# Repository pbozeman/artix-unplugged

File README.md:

# Artix Unplugged

Bare Artix-7 with all the IO pins exposed.

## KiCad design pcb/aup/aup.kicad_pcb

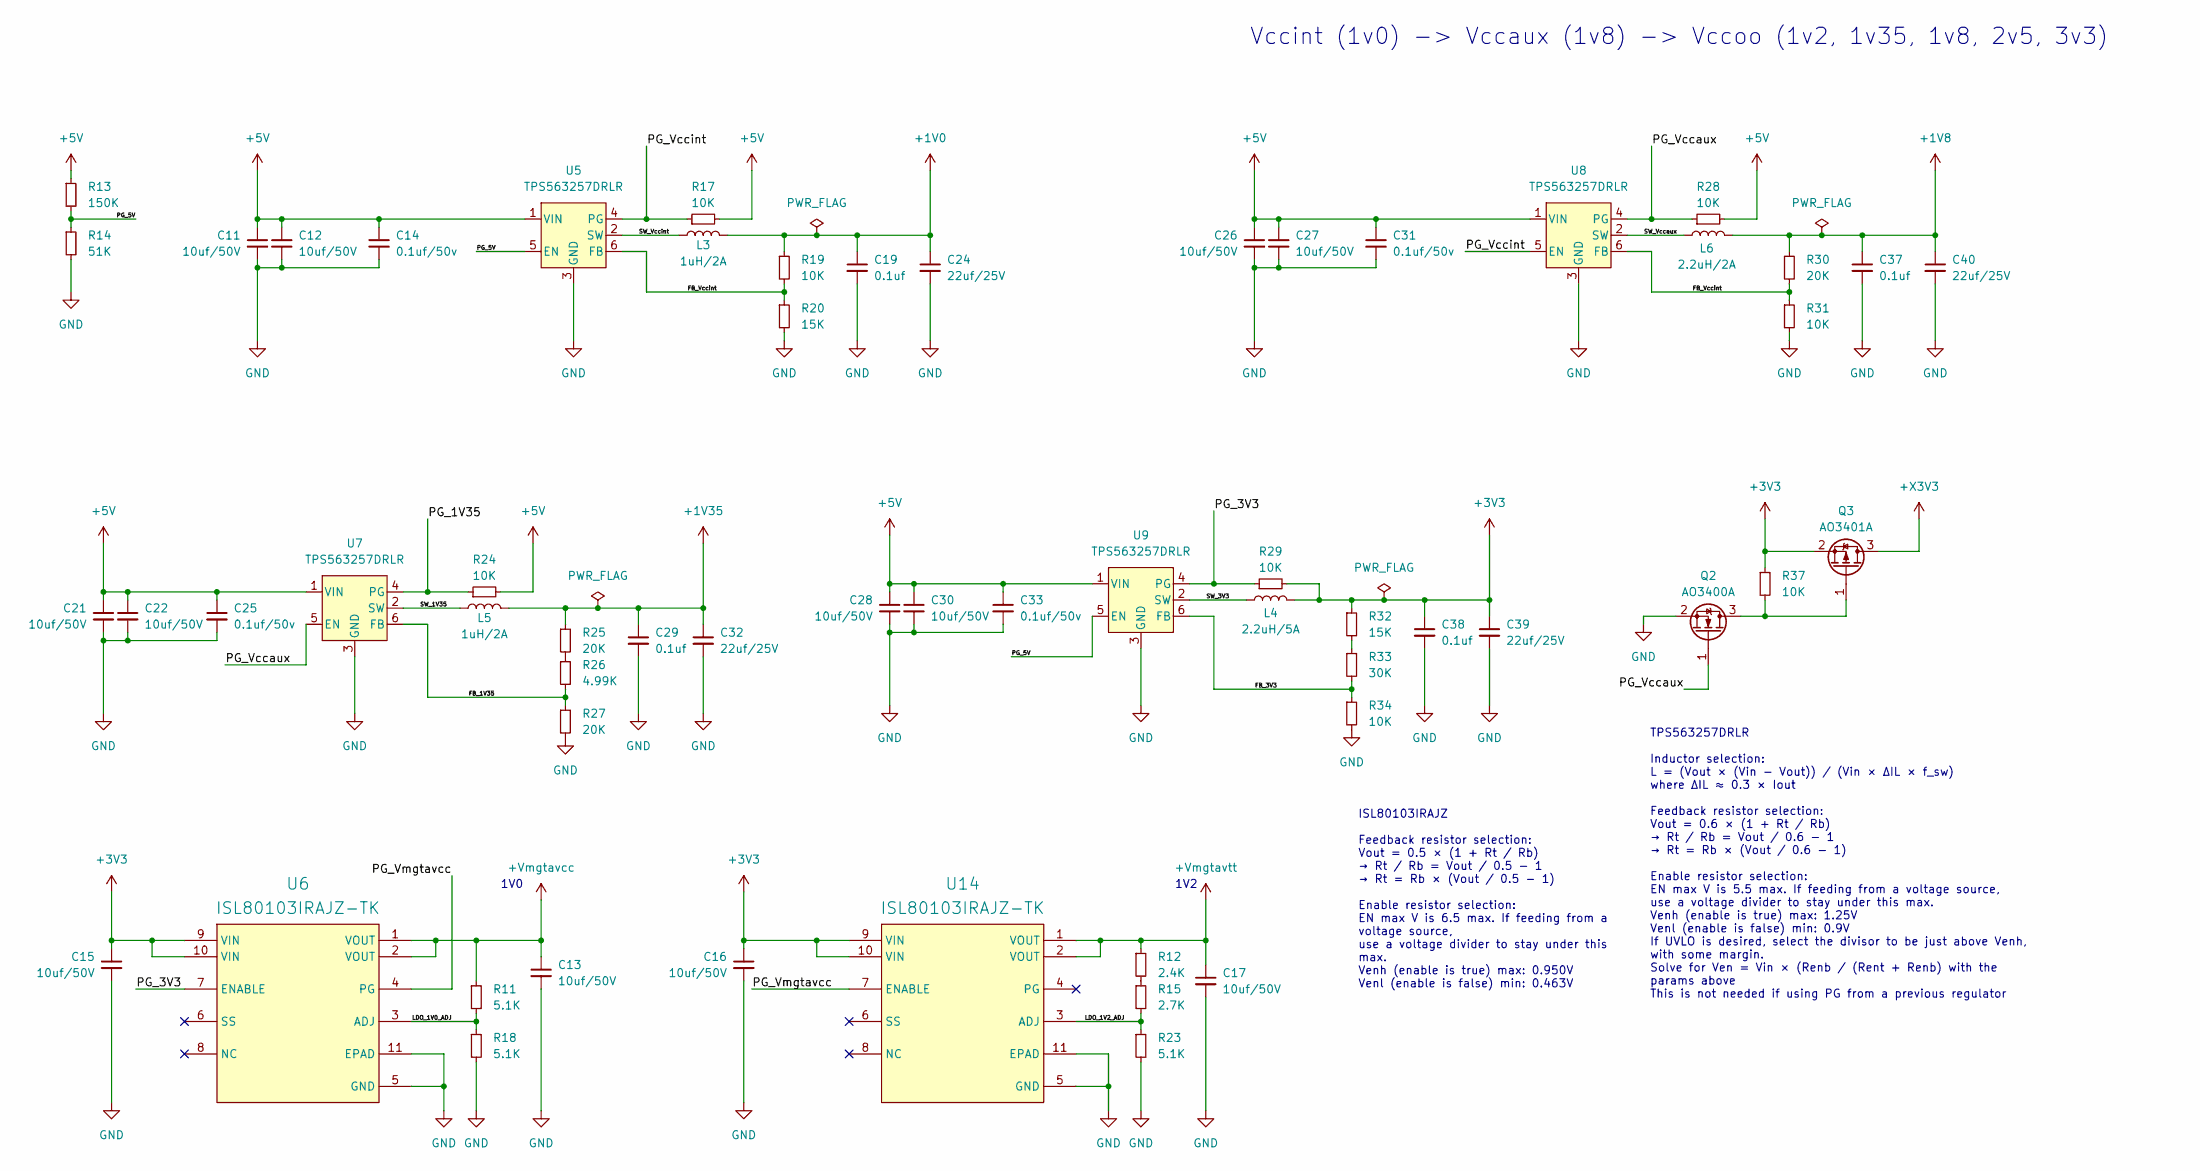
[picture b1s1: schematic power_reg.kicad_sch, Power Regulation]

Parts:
C11, C12, C13, C15, C16, C17, C21, C22, C26, C27, C28, C30: 10uf/50V; C_0805_2012Metric; LCSC Part # C440198
C14, C25, C31, C33: 0.1uf/50v; C_0603_1608Metric; LCSC Part # C14663
C19, C29, C37, C38: 0.1uf; C_0402_1005Metric; LCSC Part # C1525
C24, C32, C39, C40: 22uf/25V; C_0805_2012Metric; LCSC Part # C45783
L3, L5: 1uH/2A; L_1008_2520Metric; LCSC Part # C435392
L4: 2.2uH/5A; L_Sunlord_MWSA0518S; LCSC Part # C408345
L6: 2.2uH/2A; L_1008_2520Metric; LCSC Part # C576403
Q2: AO3400A; SOT-23; LCSC Part # C20917
Q3: AO3401A; SOT-23; LCSC Part # C15127
R11, R18, R23: 5.1K; R_0603_1608Metric; LCSC Part # C23186
R12: 2.4K; R_0603_1608Metric; LCSC Part # C22940
R13: 150K; R_0603_1608Metric; LCSC Part # C22808
R14: 51K; R_0603_1608Metric; LCSC Part # C23196
R15: 2.7K; R_0603_1608Metric; LCSC Part # C25879
R17, R19, R24, R28, R29, R31, R34, R37: 10K; R_0603_1608Metric; LCSC Part # C25804
R20, R32: 15K; R_0603_1608Metric; LCSC Part # C22809
R25, R27, R30: 20K; R_0603_1608Metric; LCSC Part # C4184
R26: 4.99K; R_0603_1608Metric; LCSC Part # C23046
R33: 30K; R_0603_1608Metric; LCSC Part # C22984
U5, U7, U8, U9: TPS563257DRLR; SOT6_DRL_TEX; LCSC Part # C20539656
U6, U14: ISL80103IRAJZ-TK; DFN10_3X3_INR; LCSC Part # C382020

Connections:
+1V0: C19.1, C24.1, L3.2, R19.1; also elsewhere on the board
+1V8: C37.1, C40.1, L6.2, R30.1; also elsewhere on the board
+1V35: C29.1, C32.1, L5.2, R25.1; also elsewhere on the board
+3V3: C15.1, C16.1, C38.1, C39.1, L4.2, Q3.2 (S), R29.2, R32.1, R37.1, U6.9 (VIN), U6.10 (VIN), U14.9 (VIN), U14.10 (VIN); also elsewhere on the board
+5V: C11.1, C12.1, C14.1, C21.1, C22.1, C25.1, C26.1, C27.1, C28.1, C30.1, C31.1, C33.1, R13.1, R17.2, R24.2, R28.2, U5.1 (VIN), U7.1 (VIN), U8.1 (VIN), U9.1 (VIN); also elsewhere on the board
+Vmgtavcc: C13.1, R11.1, U6.1 (VOUT), U6.2 (VOUT); also elsewhere on the board
+Vmgtavtt: C17.1, R12.1, U14.1 (VOUT), U14.2 (VOUT); also elsewhere on the board
+X3V3: Q3.3 (D)
/power_reg/FB_1V35: R26.2, R27.1, U7.6 (FB)
/power_reg/FB_3V3: R33.2, R34.1, U9.6 (FB)
/power_reg/FB_Vccint: R19.2, R20.1, R30.2, R31.1, U5.6 (FB), U8.6 (FB)
/power_reg/LDO_1V0_ADJ: R11.2, R18.1, U6.3 (ADJ)
/power_reg/LDO_1V2_ADJ: R15.2, R23.1, U14.3 (ADJ)
/power_reg/PG_1V35: R24.1, U7.4 (PG)
/power_reg/PG_3V3: R29.1, U6.7 (ENABLE), U9.4 (PG)
/power_reg/PG_5V: R13.2, R14.1, U5.5 (EN), U9.5 (EN)
/power_reg/PG_Vccaux: Q2.1 (G), R28.1, U7.5 (EN), U8.4 (PG)
/power_reg/PG_Vccint: R17.1, U5.4 (PG), U8.5 (EN)
/power_reg/PG_Vmgtavcc: U6.4 (PG), U14.7 (ENABLE)
/power_reg/SW_1V35: L5.1, U7.2 (SW)
/power_reg/SW_3V3: L4.1, U9.2 (SW)
/power_reg/SW_Vccaux: L6.1, U8.2 (SW)
/power_reg/SW_Vccint: L3.1, U5.2 (SW)
GND: C11.2, C12.2, C13.2, C14.2, C15.2, C16.2, C17.2, C19.2, C21.2, C22.2, C24.2, C25.2, C26.2, C27.2, C28.2, C29.2, C30.2, C31.2, C32.2, C33.2, C37.2, C38.2, C39.2, C40.2, Q2.2 (S), R14.2, R18.2, R20.2, R23.2, R27.2, R31.2, R34.2, U5.3 (GND), U6.5 (GND), U6.11 (EPAD), U7.3 (GND), U8.3 (GND), U9.3 (GND), U14.5 (GND), U14.11 (EPAD); also elsewhere on the board
unnamed: Q2.3 (D), Q3.1 (G), R37.2
unnamed: R12.2, R15.1
unnamed: R25.2, R26.1
unnamed: R32.2, R33.1

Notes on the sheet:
Vccint (1v0) -> Vccaux (1v8) -> Vccoo (1v2, 1v35, 1v8, 2v5, 3v3)
1V2
1V0
TPS563257DRLR Inductor selection: L = (Vout × (Vin - Vout)) / (Vin × ΔIL × f_sw) where ΔIL ≈ 0.3 × Iout Feedback resistor selection: Vout = 0.6 × (1 + Rt / Rb) → Rt / Rb = Vout / 0.6 - 1 → Rt = Rb × (Vout / 0.6 - 1) Enable resistor selection: EN max V is 5.5 max. If feeding from a voltage source, u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
ISL80103IRAJZ Feedback resistor selection: Vout = 0.5 × (1 + Rt / Rb) → Rt / Rb = Vout / 0.5 - 1 → Rt = Rb × (Vout / 0.5 - 1) Enable resistor selection: EN max V is 6.5 max. If feeding from a voltage source, use a voltage divider to stay under this max. Venh (enable is true) max: 0.950V Venl (enabl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

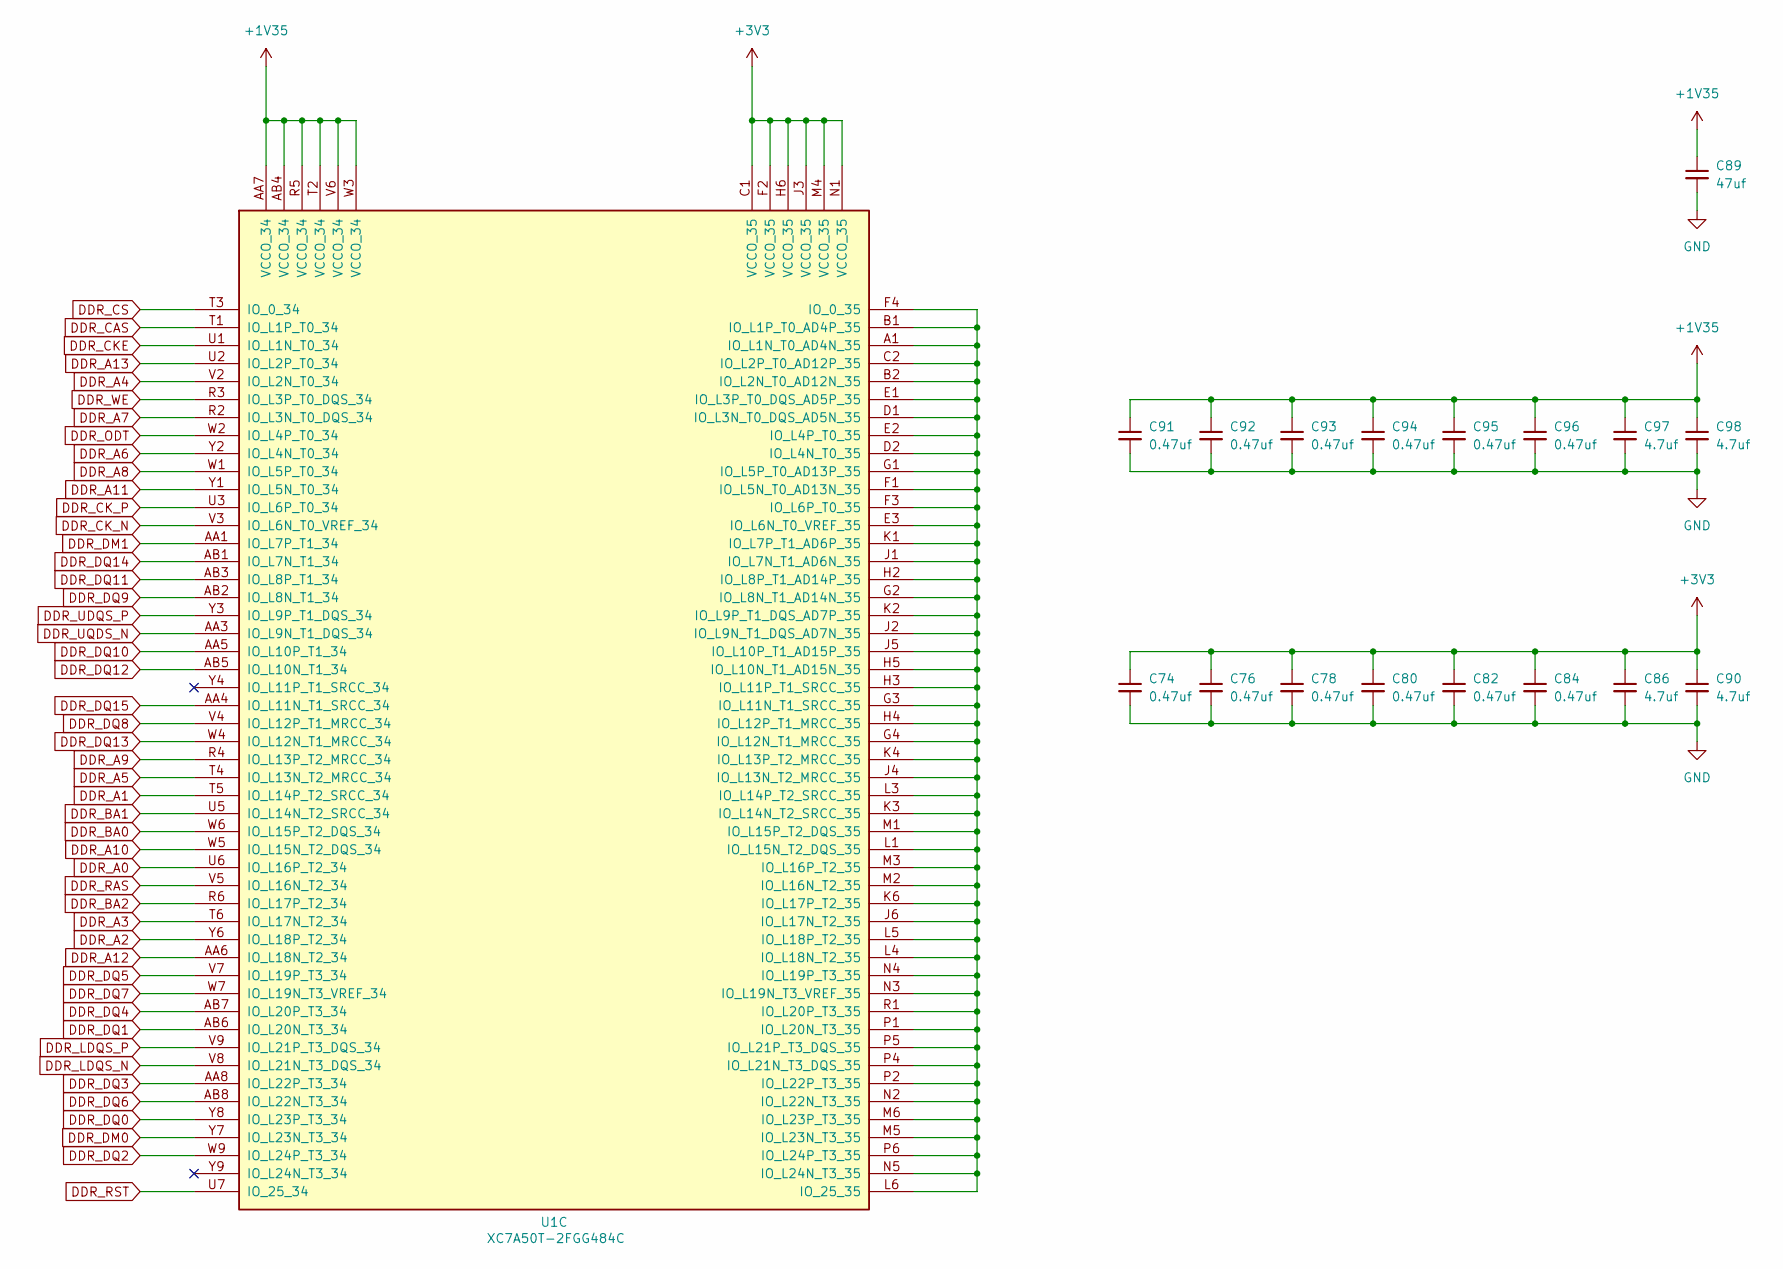
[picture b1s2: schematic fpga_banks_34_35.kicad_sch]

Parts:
C74, C76, C78, C80, C82, C84, C91, C92, C93, C94, C95, C96: 0.47uf; C_0201_0603Metric; LCSC Part # C318543
C86, C90, C97, C98: 4.7uf; C_0805_2012Metric; LCSC Part # C1779
C89: 47uf; C_1206_3216Metric; LCSC Part # C96123
U1: XC7A50T-2FGG484C; Xilinx_FGG484; LCSC Part # C1550658

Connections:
+1V35: C89.1, C91.1, C92.1, C93.1, C94.1, C95.1, C96.1, C97.1, C98.1, U1.AA7 (VCCO_34), U1.AB4 (VCCO_34), U1.R5 (VCCO_34), U1.T2 (VCCO_34), U1.V6 (VCCO_34), U1.W3 (VCCO_34); also elsewhere on the board
+3V3: C74.1, C76.1, C78.1, C80.1, C82.1, C84.1, C86.1, C90.1, U1.C1 (VCCO_35), U1.F2 (VCCO_35), U1.H6 (VCCO_35), U1.J3 (VCCO_35), U1.M4 (VCCO_35), U1.N1 (VCCO_35); also elsewhere on the board
DDR_A0: U1.U6 (IO_L16P_T2_34); also elsewhere on the board
DDR_A1: U1.T5 (IO_L14P_T2_SRCC_34); also elsewhere on the board
DDR_A2: U1.Y6 (IO_L18P_T2_34); also elsewhere on the board
DDR_A3: U1.T6 (IO_L17N_T2_34); also elsewhere on the board
DDR_A4: U1.V2 (IO_L2N_T0_34); also elsewhere on the board
DDR_A5: U1.T4 (IO_L13N_T2_MRCC_34); also elsewhere on the board
DDR_A6: U1.Y2 (IO_L4N_T0_34); also elsewhere on the board
DDR_A7: U1.R2 (IO_L3N_T0_DQS_34); also elsewhere on the board
DDR_A8: U1.W1 (IO_L5P_T0_34); also elsewhere on the board
DDR_A9: U1.R4 (IO_L13P_T2_MRCC_34); also elsewhere on the board
DDR_A10: U1.W5 (IO_L15N_T2_DQS_34); also elsewhere on the board
DDR_A11: U1.Y1 (IO_L5N_T0_34); also elsewhere on the board
DDR_A12: U1.AA6 (IO_L18N_T2_34); also elsewhere on the board
DDR_A13: U1.U2 (IO_L2P_T0_34); also elsewhere on the board
DDR_BA0: U1.W6 (IO_L15P_T2_DQS_34); also elsewhere on the board
DDR_BA1: U1.U5 (IO_L14N_T2_SRCC_34); also elsewhere on the board
DDR_BA2: U1.R6 (IO_L17P_T2_34); also elsewhere on the board
DDR_CAS: U1.T1 (IO_L1P_T0_34); also elsewhere on the board
DDR_CKE: U1.U1 (IO_L1N_T0_34); also elsewhere on the board
DDR_CK_N: U1.V3 (IO_L6N_T0_VREF_34); also elsewhere on the board
DDR_CK_P: U1.U3 (IO_L6P_T0_34); also elsewhere on the board
DDR_CS: U1.T3 (IO_0_34); also elsewhere on the board
DDR_DM0: U1.Y7 (IO_L23N_T3_34); also elsewhere on the board
DDR_DM1: U1.AA1 (IO_L7P_T1_34); also elsewhere on the board
DDR_DQ0: U1.Y8 (IO_L23P_T3_34); also elsewhere on the board
DDR_DQ1: U1.AB6 (IO_L20N_T3_34); also elsewhere on the board
DDR_DQ2: U1.W9 (IO_L24P_T3_34); also elsewhere on the board
DDR_DQ3: U1.AA8 (IO_L22P_T3_34); also elsewhere on the board
DDR_DQ4: U1.AB7 (IO_L20P_T3_34); also elsewhere on the board
DDR_DQ5: U1.V7 (IO_L19P_T3_34); also elsewhere on the board
DDR_DQ6: U1.AB8 (IO_L22N_T3_34); also elsewhere on the board
DDR_DQ7: U1.W7 (IO_L19N_T3_VREF_34); also elsewhere on the board
DDR_DQ8: U1.V4 (IO_L12P_T1_MRCC_34); also elsewhere on the board
DDR_DQ9: U1.AB2 (IO_L8N_T1_34); also elsewhere on the board
DDR_DQ10: U1.AA5 (IO_L10P_T1_34); also elsewhere on the board
DDR_DQ11: U1.AB3 (IO_L8P_T1_34); also elsewhere on the board
DDR_DQ12: U1.AB5 (IO_L10N_T1_34); also elsewhere on the board
DDR_DQ13: U1.W4 (IO_L12N_T1_MRCC_34); also elsewhere on the board
DDR_DQ14: U1.AB1 (IO_L7N_T1_34); also elsewhere on the board
DDR_DQ15: U1.AA4 (IO_L11N_T1_SRCC_34); also elsewhere on the board
DDR_LDQS_N: U1.V8 (IO_L21N_T3_DQS_34); also elsewhere on the board
DDR_LDQS_P: U1.V9 (IO_L21P_T3_DQS_34); also elsewhere on the board
DDR_ODT: U1.W2 (IO_L4P_T0_34); also elsewhere on the board
DDR_RAS: U1.V5 (IO_L16N_T2_34); also elsewhere on the board
DDR_RST: U1.U7 (IO_25_34); also elsewhere on the board
DDR_UDQS_P: U1.Y3 (IO_L9P_T1_DQS_34); also elsewhere on the board
DDR_UQDS_N: U1.AA3 (IO_L9N_T1_DQS_34); also elsewhere on the board
DDR_WE: U1.R3 (IO_L3P_T0_DQS_34); also elsewhere on the board
GND: C74.2, C76.2, C78.2, C80.2, C82.2, C84.2, C86.2, C89.2, C90.2, C91.2, C92.2, C93.2, C94.2, C95.2, C96.2, C97.2, C98.2; also elsewhere on the board
unnamed: U1.A1 (IO_L1N_T0_AD4N_35), U1.B1 (IO_L1P_T0_AD4P_35), U1.B2 (IO_L2N_T0_AD12N_35), U1.C2 (IO_L2P_T0_AD12P_35), U1.D1 (IO_L3N_T0_DQS_AD5N_35), U1.D2 (IO_L4N_T0_35), U1.E1 (IO_L3P_T0_DQS_AD5P_35), U1.E2 (IO_L4P_T0_35), U1.E3 (IO_L6N_T0_VREF_35), U1.F1 (IO_L5N_T0_AD13N_35), U1.F3 (IO_L6P_T0_35), U1.F4 (IO_0_35), U1.G1 (IO_L5P_T0_AD13P_35), U1.G2 (IO_L8N_T1_AD14N_35), U1.G3 (IO_L11N_T1_SRCC_35), U1.G4 (IO_L12N_T1_MRCC_35), U1.H2 (IO_L8P_T1_AD14P_35), U1.H3 (IO_L11P_T1_SRCC_35), U1.H4 (IO_L12P_T1_MRCC_35), U1.H5 (IO_L10N_T1_AD15N_35), U1.J1 (IO_L7N_T1_AD6N_35), U1.J2 (IO_L9N_T1_DQS_AD7N_35), U1.J4 (IO_L13N_T2_MRCC_35), U1.J5 (IO_L10P_T1_AD15P_35), U1.J6 (IO_L17N_T2_35), U1.K1 (IO_L7P_T1_AD6P_35), U1.K2 (IO_L9P_T1_DQS_AD7P_35), U1.K3 (IO_L14N_T2_SRCC_35), U1.K4 (IO_L13P_T2_MRCC_35), U1.K6 (IO_L17P_T2_35), U1.L1 (IO_L15N_T2_DQS_35), U1.L3 (IO_L14P_T2_SRCC_35), U1.L4 (IO_L18N_T2_35), U1.L5 (IO_L18P_T2_35), U1.L6 (IO_25_35), U1.M1 (IO_L15P_T2_DQS_35), U1.M2 (IO_L16N_T2_35), U1.M3 (IO_L16P_T2_35), U1.M5 (IO_L23N_T3_35), U1.M6 (IO_L23P_T3_35), U1.N2 (IO_L22N_T3_35), U1.N3 (IO_L19N_T3_VREF_35), U1.N4 (IO_L19P_T3_35), U1.N5 (IO_L24N_T3_35), U1.P1 (IO_L20N_T3_35), U1.P2 (IO_L22P_T3_35), U1.P4 (IO_L21N_T3_DQS_35), U1.P5 (IO_L21P_T3_DQS_35), U1.P6 (IO_L24P_T3_35), U1.R1 (IO_L20P_T3_35)

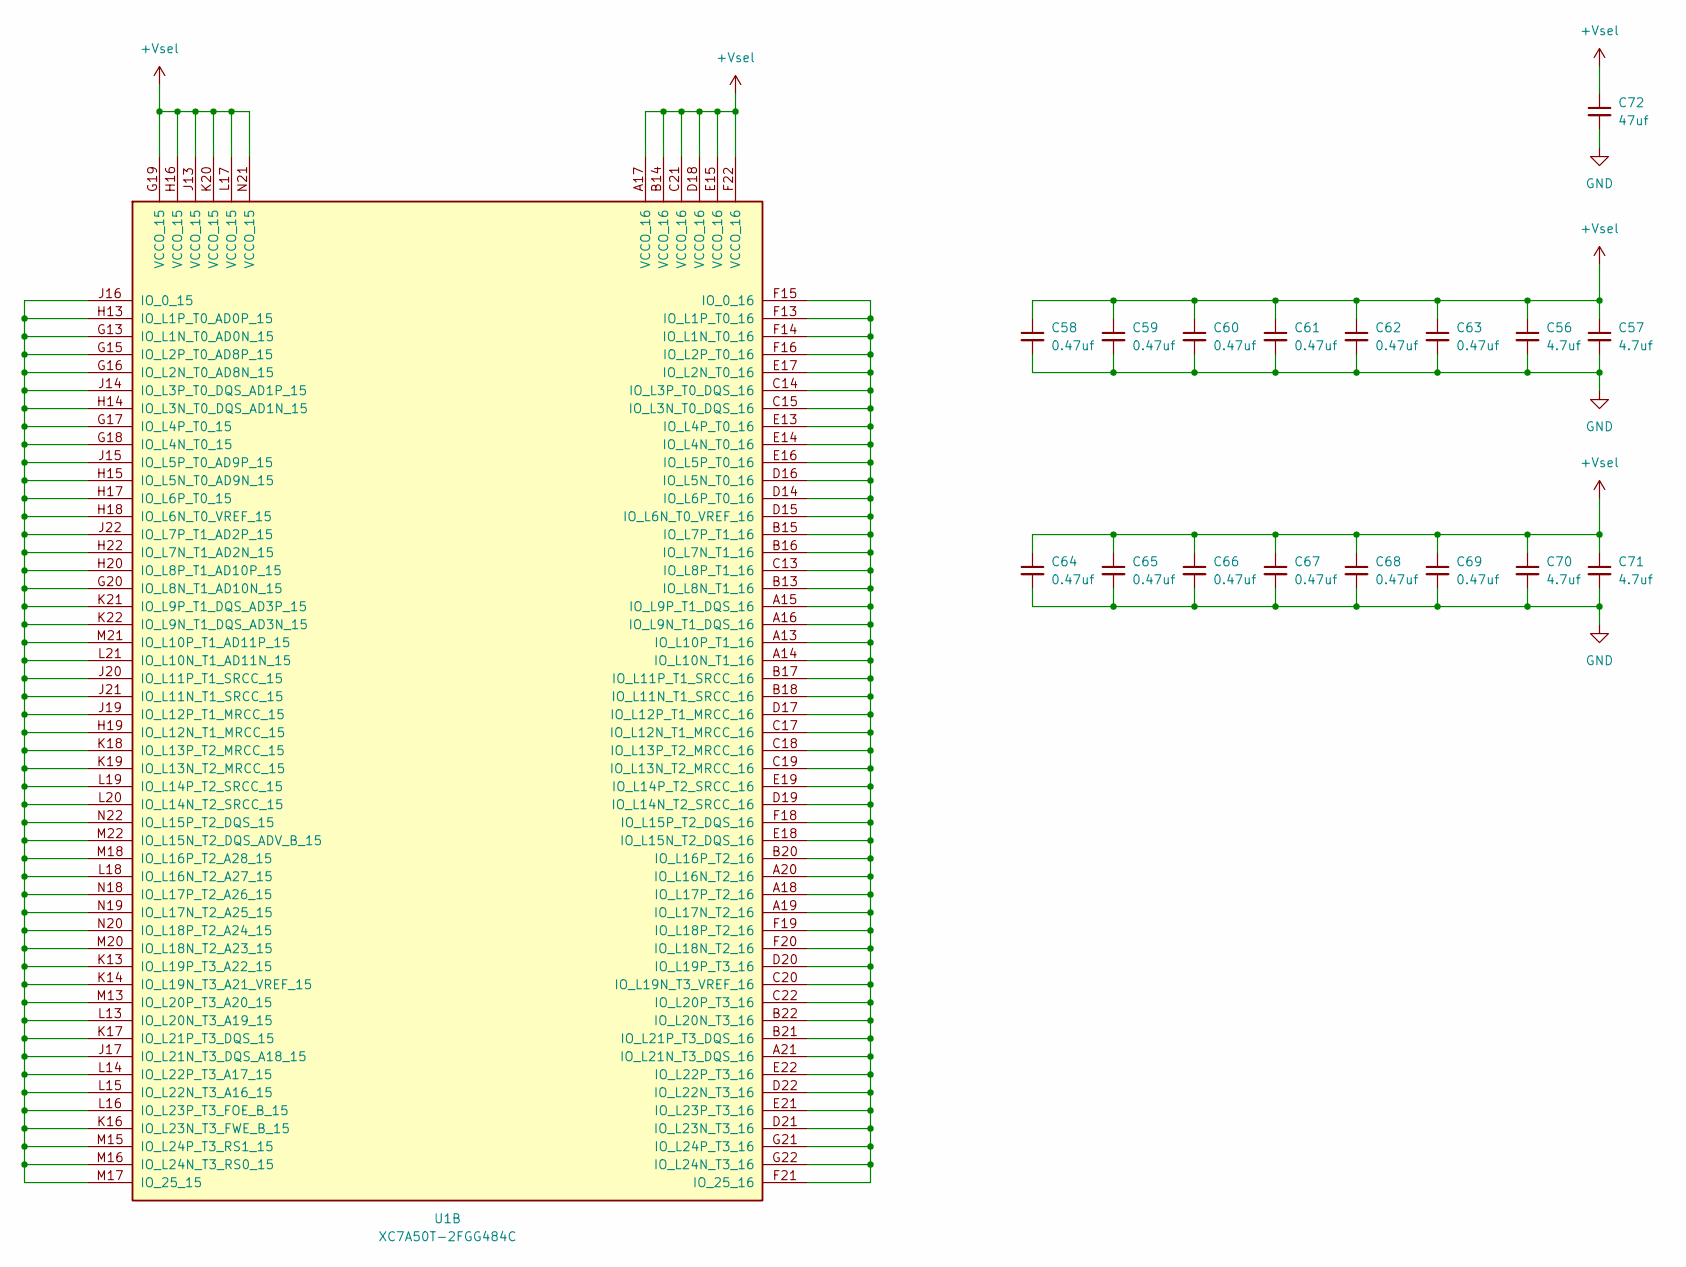
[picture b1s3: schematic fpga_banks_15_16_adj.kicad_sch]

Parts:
C56, C57, C70, C71: 4.7uf; C_0805_2012Metric; LCSC Part # C1779
C58, C59, C60, C61, C62, C63, C64, C65, C66, C67, C68, C69: 0.47uf; C_0201_0603Metric; LCSC Part # C318543
C72: 47uf; C_1206_3216Metric; LCSC Part # C96123
U1: XC7A50T-2FGG484C; Xilinx_FGG484; LCSC Part # C1550658

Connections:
+Vsel: C56.1, C57.1, C58.1, C59.1, C60.1, C61.1, C62.1, C63.1, C64.1, C65.1, C66.1, C67.1, C68.1, C69.1, C70.1, C71.1, C72.1, U1.A17 (VCCO_16), U1.B14 (VCCO_16), U1.C21 (VCCO_16), U1.D18 (VCCO_16), U1.E15 (VCCO_16), U1.F22 (VCCO_16), U1.G19 (VCCO_15), U1.H16 (VCCO_15), U1.J13 (VCCO_15), U1.K20 (VCCO_15), U1.L17 (VCCO_15), U1.N21 (VCCO_15); also elsewhere on the board
GND: C56.2, C57.2, C58.2, C59.2, C60.2, C61.2, C62.2, C63.2, C64.2, C65.2, C66.2, C67.2, C68.2, C69.2, C70.2, C71.2, C72.2; also elsewhere on the board
unnamed: U1.G13 (IO_L1N_T0_AD0N_15), U1.G15 (IO_L2P_T0_AD8P_15), U1.G16 (IO_L2N_T0_AD8N_15), U1.G17 (IO_L4P_T0_15), U1.G18 (IO_L4N_T0_15), U1.G20 (IO_L8N_T1_AD10N_15), U1.H13 (IO_L1P_T0_AD0P_15), U1.H14 (IO_L3N_T0_DQS_AD1N_15), U1.H15 (IO_L5N_T0_AD9N_15), U1.H17 (IO_L6P_T0_15), U1.H18 (IO_L6N_T0_VREF_15), U1.H19 (IO_L12N_T1_MRCC_15), U1.H20 (IO_L8P_T1_AD10P_15), U1.H22 (IO_L7N_T1_AD2N_15), U1.J14 (IO_L3P_T0_DQS_AD1P_15), U1.J15 (IO_L5P_T0_AD9P_15), U1.J16 (IO_0_15), U1.J17 (IO_L21N_T3_DQS_A18_15), U1.J19 (IO_L12P_T1_MRCC_15), U1.J20 (IO_L11P_T1_SRCC_15), U1.J21 (IO_L11N_T1_SRCC_15), U1.J22 (IO_L7P_T1_AD2P_15), U1.K13 (IO_L19P_T3_A22_15), U1.K14 (IO_L19N_T3_A21_VREF_15), U1.K16 (IO_L23N_T3_FWE_B_15), U1.K17 (IO_L21P_T3_DQS_15), U1.K18 (IO_L13P_T2_MRCC_15), U1.K19 (IO_L13N_T2_MRCC_15), U1.K21 (IO_L9P_T1_DQS_AD3P_15), U1.K22 (IO_L9N_T1_DQS_AD3N_15), U1.L13 (IO_L20N_T3_A19_15), U1.L14 (IO_L22P_T3_A17_15), U1.L15 (IO_L22N_T3_A16_15), U1.L16 (IO_L23P_T3_FOE_B_15), U1.L18 (IO_L16N_T2_A27_15), U1.L19 (IO_L14P_T2_SRCC_15), U1.L20 (IO_L14N_T2_SRCC_15), U1.L21 (IO_L10N_T1_AD11N_15), U1.M13 (IO_L20P_T3_A20_15), U1.M15 (IO_L24P_T3_RS1_15), U1.M16 (IO_L24N_T3_RS0_15), U1.M17 (IO_25_15), U1.M18 (IO_L16P_T2_A28_15), U1.M20 (IO_L18N_T2_A23_15), U1.M21 (IO_L10P_T1_AD11P_15), U1.M22 (IO_L15N_T2_DQS_ADV_B_15), U1.N18 (IO_L17P_T2_A26_15), U1.N19 (IO_L17N_T2_A25_15), U1.N20 (IO_L18P_T2_A24_15), U1.N22 (IO_L15P_T2_DQS_15)
unnamed: U1.A13 (IO_L10P_T1_16), U1.A14 (IO_L10N_T1_16), U1.A15 (IO_L9P_T1_DQS_16), U1.A16 (IO_L9N_T1_DQS_16), U1.A18 (IO_L17P_T2_16), U1.A19 (IO_L17N_T2_16), U1.A20 (IO_L16N_T2_16), U1.A21 (IO_L21N_T3_DQS_16), U1.B13 (IO_L8N_T1_16), U1.B15 (IO_L7P_T1_16), U1.B16 (IO_L7N_T1_16), U1.B17 (IO_L11P_T1_SRCC_16), U1.B18 (IO_L11N_T1_SRCC_16), U1.B20 (IO_L16P_T2_16), U1.B21 (IO_L21P_T3_DQS_16), U1.B22 (IO_L20N_T3_16), U1.C13 (IO_L8P_T1_16), U1.C14 (IO_L3P_T0_DQS_16), U1.C15 (IO_L3N_T0_DQS_16), U1.C17 (IO_L12N_T1_MRCC_16), U1.C18 (IO_L13P_T2_MRCC_16), U1.C19 (IO_L13N_T2_MRCC_16), U1.C20 (IO_L19N_T3_VREF_16), U1.C22 (IO_L20P_T3_16), U1.D14 (IO_L6P_T0_16), U1.D15 (IO_L6N_T0_VREF_16), U1.D16 (IO_L5N_T0_16), U1.D17 (IO_L12P_T1_MRCC_16), U1.D19 (IO_L14N_T2_SRCC_16), U1.D20 (IO_L19P_T3_16), U1.D21 (IO_L23N_T3_16), U1.D22 (IO_L22N_T3_16), U1.E13 (IO_L4P_T0_16), U1.E14 (IO_L4N_T0_16), U1.E16 (IO_L5P_T0_16), U1.E17 (IO_L2N_T0_16), U1.E18 (IO_L15N_T2_DQS_16), U1.E19 (IO_L14P_T2_SRCC_16), U1.E21 (IO_L23P_T3_16), U1.E22 (IO_L22P_T3_16), U1.F13 (IO_L1P_T0_16), U1.F14 (IO_L1N_T0_16), U1.F15 (IO_0_16), U1.F16 (IO_L2P_T0_16), U1.F18 (IO_L15P_T2_DQS_16), U1.F19 (IO_L18P_T2_16), U1.F20 (IO_L18N_T2_16), U1.F21 (IO_25_16), U1.G21 (IO_L24P_T3_16), U1.G22 (IO_L24N_T3_16)

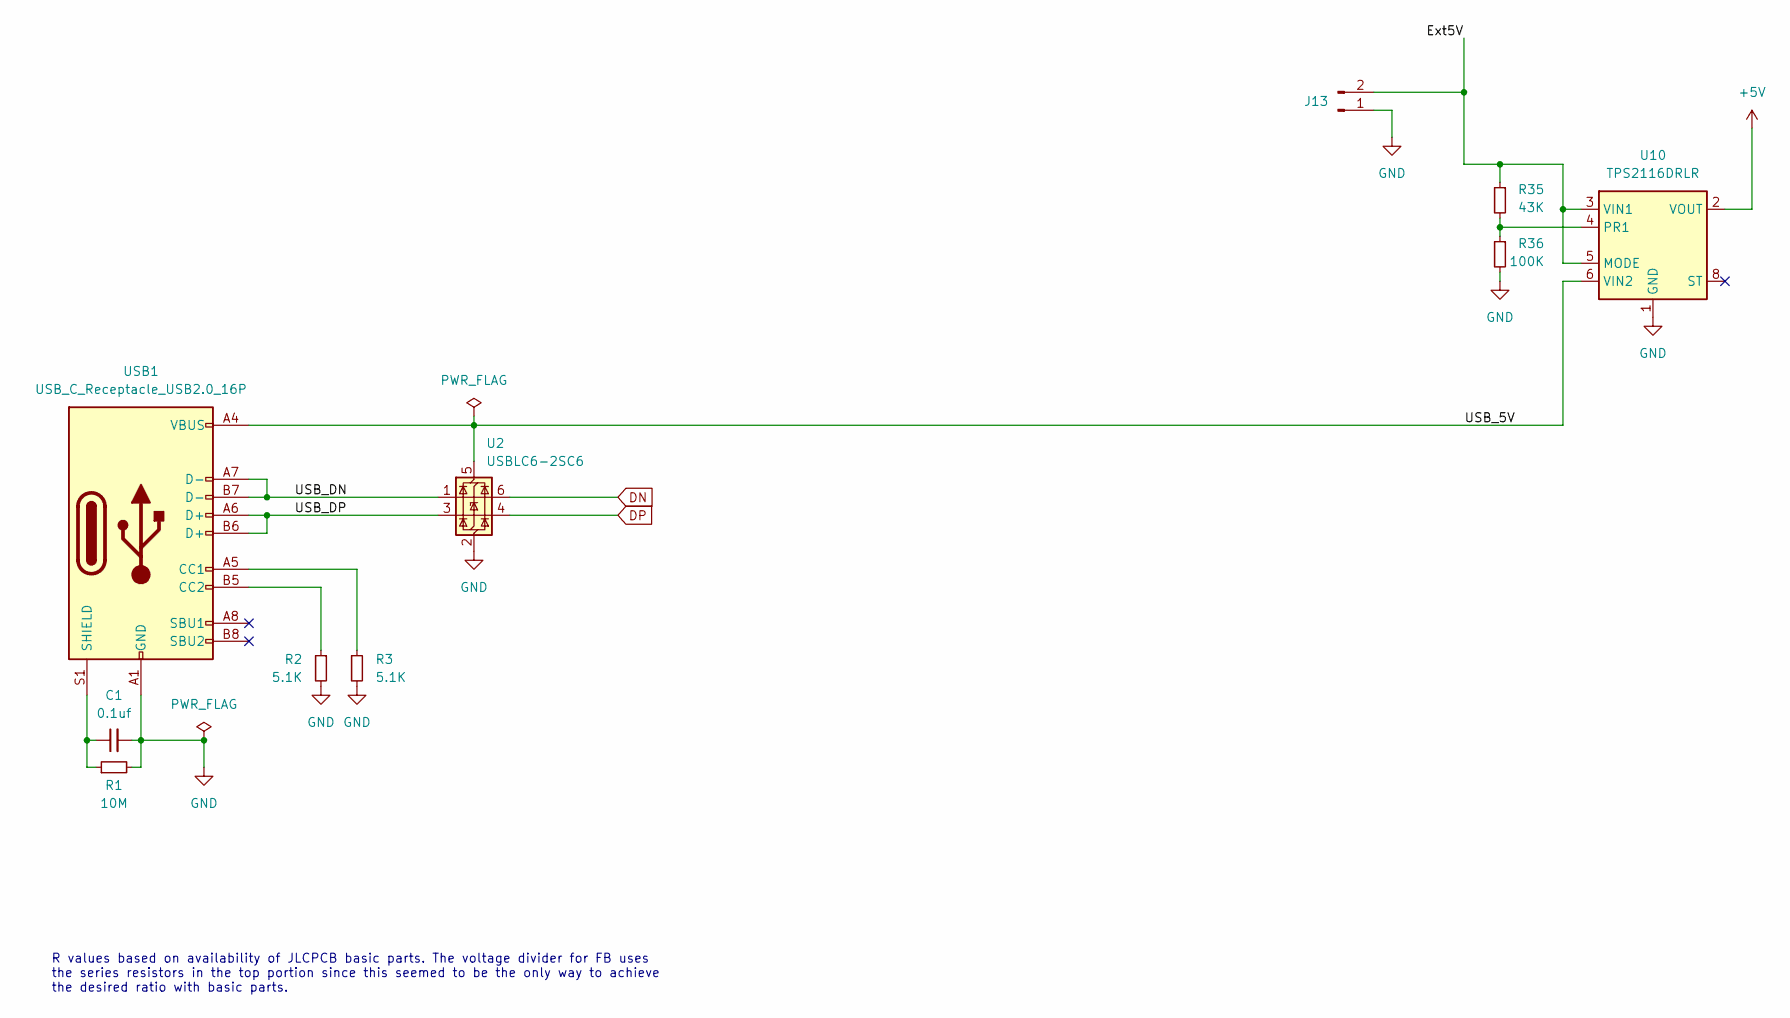
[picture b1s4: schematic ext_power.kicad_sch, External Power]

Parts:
C1: 0.1uf; C_0402_1005Metric; LCSC Part # C1525
J13: Conn_01x02_Pin
R1: 10M; R_0603_1608Metric; LCSC Part # C7250
R2, R3: 5.1K; R_0603_1608Metric; LCSC Part # C23186
R35: 43K; R_0603_1608Metric; LCSC Part # C23172
R36: 100K; R_0603_1608Metric; LCSC Part # C25803
U2: USBLC6-2SC6; SOT-23-6; LCSC Part # C7519
U10: TPS2116DRLR; SOT-583-8; LCSC Part # C3235557
USB1: USB_C_Receptacle_USB2.0_16P; USB_C_Receptacle_GCT_USB4105-xx-A_16P_TopMnt_Horizontal; LCSC Part # C2686968

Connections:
+5V: U10.2 (VOUT), U10.7 (VOUT); also elsewhere on the board
/ext_power/Ext5V: J13.2, R35.1, U10.3 (VIN1), U10.5 (MODE)
/ext_power/USB_5V: U2.5 (VBUS), U10.6 (VIN2), USB1.A4 (VBUS), USB1.A9 (VBUS), USB1.B4 (VBUS), USB1.B9 (VBUS)
/ext_power/USB_DN: U2.1 (I/O1), USB1.A7 (D-), USB1.B7 (D-)
/ext_power/USB_DP: U2.3 (I/O2), USB1.A6 (D+), USB1.B6 (D+)
DN: U2.6 (I/O1)
DP: U2.4 (I/O2)
GND: C1.2, J13.1, R1.2, R2.2, R3.2, R36.2, U2.2 (GND), U10.1 (GND), USB1.A1 (GND), USB1.A12 (GND), USB1.B1 (GND), USB1.B12 (GND); also elsewhere on the board
unnamed: R35.2, R36.1, U10.4 (PR1)
unnamed: R3.1, USB1.A5 (CC1)
unnamed: R2.1, USB1.B5 (CC2)
unnamed: C1.1, R1.1, USB1.S1 (SHIELD)

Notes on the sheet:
R values based on availability of JLCPCB basic parts. The voltage divider for FB uses the series resistors in the top portion since this seemed to be the only way to achieve the desired ratio with basic parts.

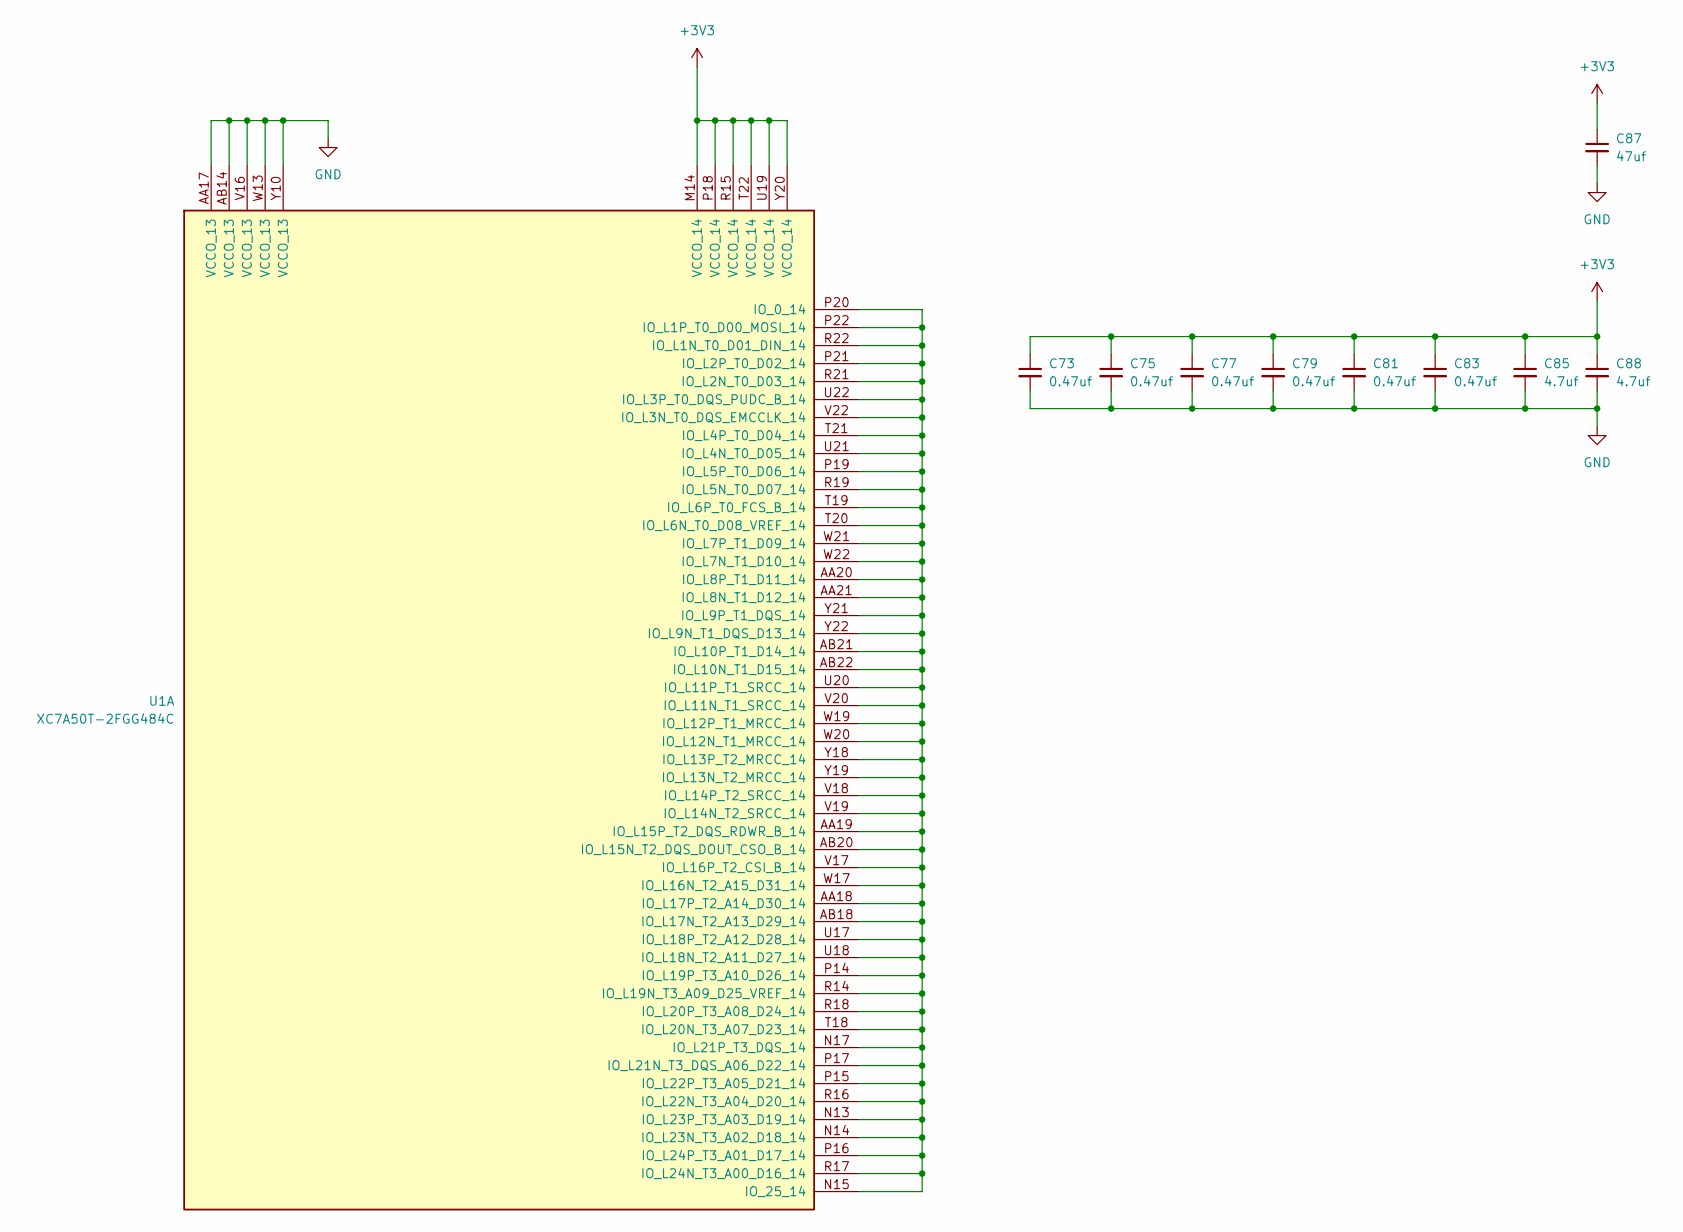
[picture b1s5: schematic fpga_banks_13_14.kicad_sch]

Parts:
C73, C75, C77, C79, C81, C83: 0.47uf; C_0201_0603Metric; LCSC Part # C318543
C85, C88: 4.7uf; C_0805_2012Metric; LCSC Part # C1779
C87: 47uf; C_1206_3216Metric; LCSC Part # C96123
U1: XC7A50T-2FGG484C; Xilinx_FGG484; LCSC Part # C1550658

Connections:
+3V3: C73.1, C75.1, C77.1, C79.1, C81.1, C83.1, C85.1, C87.1, C88.1, U1.M14 (VCCO_14), U1.P18 (VCCO_14), U1.R15 (VCCO_14), U1.T22 (VCCO_14), U1.U19 (VCCO_14), U1.Y20 (VCCO_14); also elsewhere on the board
GND: C73.2, C75.2, C77.2, C79.2, C81.2, C83.2, C85.2, C87.2, C88.2, U1.AA17 (VCCO_13), U1.AB14 (VCCO_13), U1.V16 (VCCO_13), U1.W13 (VCCO_13), U1.Y10 (VCCO_13); also elsewhere on the board
unnamed: U1.AA18 (IO_L17P_T2_A14_D30_14), U1.AA19 (IO_L15P_T2_DQS_RDWR_B_14), U1.AA20 (IO_L8P_T1_D11_14), U1.AA21 (IO_L8N_T1_D12_14), U1.AB18 (IO_L17N_T2_A13_D29_14), U1.AB20 (IO_L15N_T2_DQS_DOUT_CSO_B_14), U1.AB21 (IO_L10P_T1_D14_14), U1.AB22 (IO_L10N_T1_D15_14), U1.N13 (IO_L23P_T3_A03_D19_14), U1.N14 (IO_L23N_T3_A02_D18_14), U1.N15 (IO_25_14), U1.N17 (IO_L21P_T3_DQS_14), U1.P14 (IO_L19P_T3_A10_D26_14), U1.P15 (IO_L22P_T3_A05_D21_14), U1.P16 (IO_L24P_T3_A01_D17_14), U1.P17 (IO_L21N_T3_DQS_A06_D22_14), U1.P19 (IO_L5P_T0_D06_14), U1.P20 (IO_0_14), U1.P21 (IO_L2P_T0_D02_14), U1.P22 (IO_L1P_T0_D00_MOSI_14), U1.R14 (IO_L19N_T3_A09_D25_VREF_14), U1.R16 (IO_L22N_T3_A04_D20_14), U1.R17 (IO_L24N_T3_A00_D16_14), U1.R18 (IO_L20P_T3_A08_D24_14), U1.R19 (IO_L5N_T0_D07_14), U1.R21 (IO_L2N_T0_D03_14), U1.R22 (IO_L1N_T0_D01_DIN_14), U1.T18 (IO_L20N_T3_A07_D23_14), U1.T19 (IO_L6P_T0_FCS_B_14), U1.T20 (IO_L6N_T0_D08_VREF_14), U1.T21 (IO_L4P_T0_D04_14), U1.U17 (IO_L18P_T2_A12_D28_14), U1.U18 (IO_L18N_T2_A11_D27_14), U1.U20 (IO_L11P_T1_SRCC_14), U1.U21 (IO_L4N_T0_D05_14), U1.U22 (IO_L3P_T0_DQS_PUDC_B_14), U1.V17 (IO_L16P_T2_CSI_B_14), U1.V18 (IO_L14P_T2_SRCC_14), U1.V19 (IO_L14N_T2_SRCC_14), U1.V20 (IO_L11N_T1_SRCC_14), U1.V22 (IO_L3N_T0_DQS_EMCCLK_14), U1.W17 (IO_L16N_T2_A15_D31_14), U1.W19 (IO_L12P_T1_MRCC_14), U1.W20 (IO_L12N_T1_MRCC_14), U1.W21 (IO_L7P_T1_D09_14), U1.W22 (IO_L7N_T1_D10_14), U1.Y18 (IO_L13P_T2_MRCC_14), U1.Y19 (IO_L13N_T2_MRCC_14), U1.Y21 (IO_L9P_T1_DQS_14), U1.Y22 (IO_L9N_T1_DQS_D13_14)
